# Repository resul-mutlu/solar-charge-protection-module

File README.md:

# Solar Charge Protection Module (v1.0 Baseline)

## Project Overview
A robust, hardware-level protection baseline for solar charging systems. This module is designed to prevent reverse current leakage from batteries to solar panels during low-light conditions and protect the battery from overvoltage events using a Zener-clamped dissipation architecture. 

This repository serves as the foundational hardware layer (v1.0) before transitioning to active microcontroller-based power management.

## Hardware Architecture & Component Selection
Instead of blindly relying on generic components, each part was selected with specific power-efficiency and safety metrics in mind:
* **Reverse Current Protection (D1 - 1N5819 Schottky Diode):** Selected over standard silicon diodes (e.g., 1N4007) to minimize forward voltage drop (approx. 0.2V - 0.3V vs. 0.7V). This significantly reduces thermal dissipation (W = V * I) and maximizes power transfer efficiency from the panel to the battery.
* **Overvoltage Clamping (D2 - 15V Zener Diode):** Configured as a shunt regulator to ground. If the solar panel output exceeds the safe 15V threshold, the Zener diode enters breakdown mode, safely routing excess dangerous currents to GND and locking the system voltage at 15V to prevent battery swelling or explosion.
* **Current Limiting (R1 - 10R Resistor):** Prevents catastrophic current surges through the Zener diode during extreme overvoltage events.

## Simulation & Validation (LTspice)
Prior to physical PCB layout, the electrical limits of the circuit were strictly validated using LTspice to ensure thermal stability:
* **Clamping Verification:** Simulated with an 18V ideal pulse source and a realistic internal series resistance. The node voltage successfully flatlined at exactly 15V, proving the Zener diode's protection capability.
* **Dynamic Response:** Verified the zero-current state of the Zener diode when system voltage is within safe limits (<15V).

* **Red Trace `V(n001)`:** Solar Panel Input Voltage (surging to ~18V).
* **Blue Trace `V(n002)`:** Node/Battery Voltage (safely clamped at the 15V limit).
* **Green Trace `-I(D2)`:** Zener Diode Shunt Current (activating only when input > 15V, limited to safe levels by R1).

## PCB Layout & Physical Design (KiCad)
The conceptual schematic was translated into a manufacturing-ready physical board using KiCad:
* **High-Current Routing:** All power traces on the bottom copper layer (`B.Cu`) are routed at a robust **1.0 mm width** to handle sustained solar currents without thermal degradation.
* **Mechanical Stability:** Utilized Through-Hole Technology (THT) and robust Phoenix screw terminals for mechanical reliability in physical field-testing environments.

## Future Roadmap
* **v2.0 (Active MPPT):** Upgrading this passive protection baseline by integrating an STM32 microcontroller and a Buck Converter topology to achieve >90% efficiency using Maximum Power Point Tracking (MPPT) algorithms, eliminating Zener thermal losses.

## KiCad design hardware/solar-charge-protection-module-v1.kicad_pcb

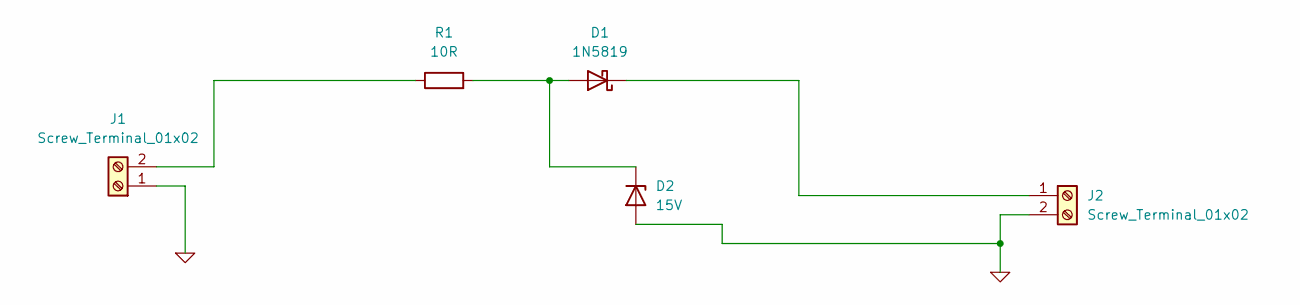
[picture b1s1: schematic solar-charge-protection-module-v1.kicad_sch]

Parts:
D1: 1N5819; D_DO-41_SOD81_P10.16mm_Horizontal
D2: 15V; D_DO-35_SOD27_P7.62mm_Horizontal
J1, J2: Screw_Terminal_01x02; TerminalBlock_Phoenix_MKDS-1,5-2-5.08_1x02_P5.08mm_Horizont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
R1: 10R; R_Axial_DIN0207_L6.3mm_D2.5mm_P10.16mm_Horizontal

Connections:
0: D2.2 (A), J1.1, J2.2
unnamed: D1.2 (A), D2.1 (K), R1.2
unnamed: D1.1 (K), J2.1
unnamed: J1.2, R1.1

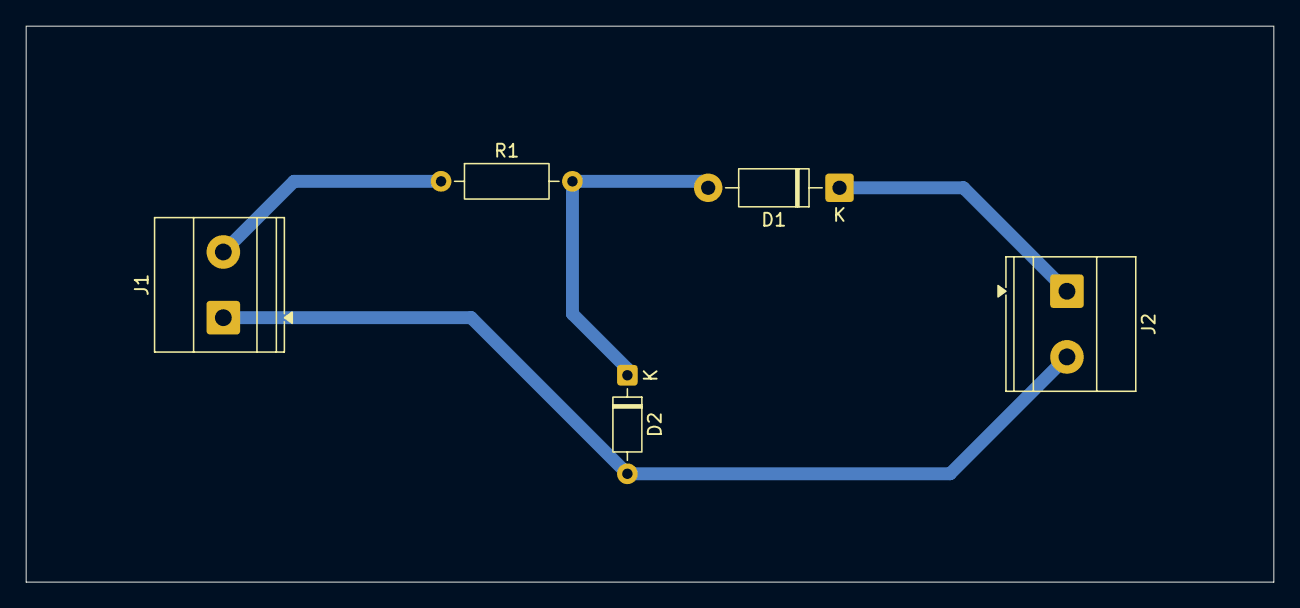
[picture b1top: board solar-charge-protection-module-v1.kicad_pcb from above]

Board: 2 copper layers, 96.5 x 43.0 mm, 5 parts (0 on the bottom side), 4 nets.

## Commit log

2026-02-21 Create simulation
2026-02-21 Create a
